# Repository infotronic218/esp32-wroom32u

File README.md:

"# esp32-wroom32u" 
"# esp32-wroom32u"

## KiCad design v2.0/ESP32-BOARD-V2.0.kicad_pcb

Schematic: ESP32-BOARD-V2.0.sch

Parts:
B1, B2: BUT; SW_Push_1P1T_NO_CK_KMR2; MPN KMR221GLFS; Mouser 611-KMR221G-LFS
C1, C2, C5, C9, C14: 1uF; C_0805_2012Metric; MPN EMK212B7105KG-T; Mouser 963-EMK212B7105KG-T
C3, C4, C7, C8, C11, C12, C13, C16: 100nF; C_0603_1608Metric; MPN C0603C104J4RAC; Mouser 80-C0603C104J4RAC
C6, C10, C15: 10uF; C_1206_3216Metric; MPN C1206C106K8PAC; Mouser 80-C1206C106K8PAC
D1, D4, D5, D6: RED; LED_0805_2012Metric; MPN AP2012HD; Mouser 604-AP2012HD
D2: YELLOW; LED_0805_2012Metric; MPN AP2012YD; Mouser 604-AP2012YD
D3, D9: GREEN; LED_0805_2012Metric; MPN 150080GS75000; Mouser 710-150080GS75000
D7: IN-PI554FCH; LED-DIGITAL-IN-PI554FCH; MPN IN-PI554FCH; Mouser 743-IN-PI554FCH
D8: RB060LAM-40TFTR; D_SOD-128; MPN RB060LAM-40TFTR; Mouser 755-RB060LAM-40TFTR
H1, H2, H3, H4: Mount; MountingHole_2.2mm_M2_Pad
J1: PIR SENSOR; PinSocket_1x03_P2.54mm_Vertical
J2: OLED-128X64; PinSocket_1x04_P2.54mm_Vertical
J3: PROG; PinHeader_1x04_P2.54mm_Vertical
J4: BATT; JST_XH_B2B-XH-A_1x02_P2.50mm_Vertical
J5: Conn_01x09; PinHeader_1x09_P2.54mm_Vertical
J6: UART; PinHeader_1x04_P2.54mm_Vertical
J7: SWITCH; SW_DIP_SPSTx04_Slide_Copal_CHS-04A_W5.08mm_P1.27mm_JPin; MPN CHS-04A; Mouser 229-CHS-04A
J8: CON_USB_GCT_USB4105_REVA; PARTREV 0.2; Mouser 640-USB4105-GF-A-060
JP1, JP2, JP3, JP4, JP5: WIRE; SolderJumper-2_P1.3mm_Open_RoundedPad1.0x1.5mm
L1: 2.2uH; L_1008_2520Metric_Pad1.43x2.20mm_HandSolder; MPN DFE252012P-2R2M=P2; Mouser 81-DFE252012P-2R2MP2
Q1: MBT3904DW1; SOT-363_SC-70-6
Q2: MIC94052YC6-TR; SOT-363_SC-70-6; MPN MIC94052YC6-TR; Mouser 998-MIC94052YC6TR
R1, R4, R5, R8, R10, R11, R27: 1.5K; R_0805_2012Metric; MPN RCC08051K50FKEA; Mouser 71-RCC08051K50FKEA
R2, R3: 470R; R_0805_2012Metric; MPN CR0805-FX-4700ELF; Mouser 652-CR0805FX-4700ELF
R6, R7, R9, R12, R13, R14, R15, R16, R17, R18, R19, R20, R21, R22, R24, R25, R26: 10K; R_0805_2012Metric; MPN CHP0805-FX-1002ELF; Mouser 652-CHP0805FX1002ELF
R23: 100K; R_0805_2012Metric; MPN CHP0805AFX-1003ELF; Mouser 652-CHP0805AFX1003EL
SW1: RST; SW_Push_1P1T_NO_CK_KMR2; MPN KMR221GLFS; Mouser 611-KMR221G-LFS
SW2: EN; SW_Push_1P1T_NO_CK_KMR2; MPN KMR221GLFS; Mouser 611-KMR221G-LFS
SW3: ON/OFF; SW_SPDT_PCM12; MPN PCM12SMTR; Mouser 611-PCM12SMTR
TH1: 10K; R_0805_2012Metric; MPN CRT0805-BY-1002ELF; Mouser 652-CRT0805BY1002ELF
U1: IC-BATT-CHARGER-MCP73834; DFN-10-1EP_3x3mm_P0.5mm_EP1.55x2.48mm; MPN MCP73834T-FCI/MF; Mouser 579-MCP73834T-FCI/MF
U2: ESP32-WROOM-32U; MPN ESP32-WROOM-32U(M113DH3200UH3Q0); Mouser 356-ESP32-WROOM-32U
U3: ADXL343; LGA-14_3x5mm_P0.8mm_LayoutBorder1x6y; MPN ADXL343BCCZ-RL7; Mouser 584-ADXL343BCCZ-R
U4: ISL9110IRTNZ; IC_BUCK_BOOST_ISL9110IRTNZ; MPN ISL9110IRTNZ; Mouser 968-ISL9110IRTNZ
U5: MIC280-3YM6-TR; SOT-23-6; MPN MIC280-3YM6-TR; Mouser 998-MIC280-3YM6TR
U6: CH340C; SOIC-16_3.9x9.9mm_P1.27mm

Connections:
+3V3: C3.1, C6.2, C7.1, C8.1, C9.2, C11.1, C15.2, C16.1, D7.3 (VDD), D9.2 (A), J1.1, J2.2 (VCC), J3.1, J5.1, J6.1, J7.5, J7.6, J7.7, J7.8, R18.1, R19.1, R24.1, R25.1, R26.1, TH1.1, U2.2 (3V3), U3.1 (Vdd_I/O), U3.6 (Vs), U3.7 (~CS), U4.1 (VOUT), U4.12 (FB), U5.1 (VDD)
+BATT: C2.1, C4.1, J4.1, Q2.1 (D), Q2.2 (S), Q2.5 (D), Q2.6 (D), U1.9 (VBAT), U1.10 (VBAT)
/D+: J8.A6 (DP1), J8.B6 (DP2), U6.5 (UD+)
/D-: J8.A7 (DN1), J8.B7 (DN2), U6.6 (UD-)
B1: B1.2, R14.1, U2.6 (I034)
B2: B2.2, R12.1, U2.7 (I035)
EN: C5.2, Q1.6 (C1), R19.2, SW2.2, U2.3 (EN)
GND: B1.1, B2.1, C1.2, C2.2, C3.2, C4.2, C5.1, C6.1, C7.2, C8.2, C9.1, C10.1, C11.2, C12.1, C13.2, C14.1, C15.1, C16.2, D7.1 (VSS), J1.3, J2.1 (GND), J3.4, J4.2, J5.9, J6.4, J8.A1/B12 (GND), J8.B1/A12 (GND), J8.G1 (GND), J8.G2 (GND), J8.G3 (GND), J8.G4 (GND), JP2.2, JP4.2, JP5.2, R1.2, R4.2, R5.2, R8.2, R9.2, R12.2, R13.2, R14.2, R15.2, R16.2, R17.2, R20.2, R23.2, R27.2, SW1.1, SW2.1, SW3.1 (A), U1.5 (VSS), U1.11 (PAD), U2.1 (GND), U2.15 (GND), U2.38 (GND), U2.G.1 (GND), U2.G.2 (GND), U2.G.4 (GND), U2.G.5 (GND), U2.G.6 (GND), U2.G.7 (GND), U2.G.8 (GND), U2.G.9 (GND), U2.G.10 (GND), U2.G.11 (GND), U2.G.12 (GND), U2.G.13 (GND), U2.G.14 (GND), U2.G.15 (GND), U2.G.16 (GND), U2.G.17 (GND), U2.G.18 (GND), U2.G.19 (GND), U2.G.20 (GND), U2.G.21 (GND), U2.G.22 (GND), U3.2 (GND), U3.4 (GND), U3.5 (GND), U3.12 (SDO/ADDR), U4.3 (PGND), U4.11 (GND), U4.13 (PAD), U5.2 (GND), U6.1 (GND)
INT: R24.2, U5.6 (~INT)
IO0: Q1.3 (C2), R18.2, SW1.2, U2.25 (IO0)
IO2: J5.7, U2.24 (IO2)
IO4: J5.8, U2.26 (IO4)
IO12: J5.5, U2.14 (IO12)
IO13_ADC2_CH4_NTC: R20.1, TH1.2, U2.16 (IO13)
IO14: J5.6, U2.13 (IO14)
IO15_PIR_IN: J1.2, U2.23 (IO15)
IO16_U2RXD: J6.2, U2.27 (IO16)
IO17_U2TXD: J6.3, U2.28 (IO17)
IO21_I2C_SDA: J2.4 (SDA), R25.2, U2.33 (IO21), U3.13 (SDA/SDI/SDIO), U5.5 (DATA)
IO22_I2C_SCL: J2.3 (SCL), R26.2, U2.36 (IO22), U3.14 (SCL/SCLK), U5.4 (CLK)
LED1: D1.2 (A), U2.31 (IO19)
LED2: D4.2 (A), U2.30 (IO18)
LED3: D5.2 (A), U2.29 (IO5)
LED4: J5.4, JP3.1, U2.37 (IO23)
LED_IN: D7.2 (DIN), U2.8 (I032)
unnamed: C10.2, D8.1 (K), Q2.4 (S), SW3.3 (C), U4.5 (PVIN), U4.6 (VIN), U4.10 (MODE/SYNC)
unnamed: C12.2, U6.4 (V3)
unnamed: D1.1 (K), R1.1
unnamed: D2.1 (K), R2.2
unnamed: D3.1 (K), R3.2
unnamed: D4.1 (K), R4.1
unnamed: D5.1 (K), R5.1
unnamed: D6.1 (K), R8.1
unnamed: D6.2 (A), JP3.2
unnamed: D9.1 (K), R27.1
unnamed: JP1.2, R6.1
unnamed: JP2.1, R7.2
unnamed: JP4.1, R10.2
unnamed: JP5.1, R11.2
unnamed: L1.1, U4.4 (LX1)
unnamed: L1.2, U4.2 (LX2)
unnamed: Q1.2 (B1), R21.1
unnamed: Q1.5 (B2), R22.1
unnamed: R2.1, U1.3 (STAT1)
unnamed: R3.1, U1.4 (STAT2)
unnamed: R6.2, R7.1, U1.7 (~PG)
unnamed: R9.1, U1.8 (THERM)
unnamed: R10.1, R11.1, U1.6 (PROG)
unnamed: SW3.2 (B), U4.9 (EN)
S1: J7.1, R13.1, U2.9 (I033)
S2: J7.2, R15.1, U2.10 (I025)
S3: J7.3, R16.1, U2.11 (I026)
S4: J7.4, R17.1, U2.12 (IO27)
U0RXD: J3.2, U2.35 (TXD0), U6.2 (TXD)
U0TXD: J3.3, U2.34 (RXD0), U6.3 (RXD)
VBUS: C1.1, C13.1, C14.2, D2.2 (A), D3.2 (A), D8.2 (A), J8.A4/B9 (VBUS), J8.B4/A9 (VBUS), JP1.1, Q2.3 (G), R23.1, U1.1 (VDD), U1.2 (VDD), U6.16 (VCC)
VN: J5.3, U2.5 (SENSOR_VN)
VP: J5.2, U2.4 (SENSOR_VP)
~DTR: Q1.4 (E2), R21.2, U6.13 (~DTR)
~RTS: Q1.1 (E1), R22.2, U6.14 (~RTS)

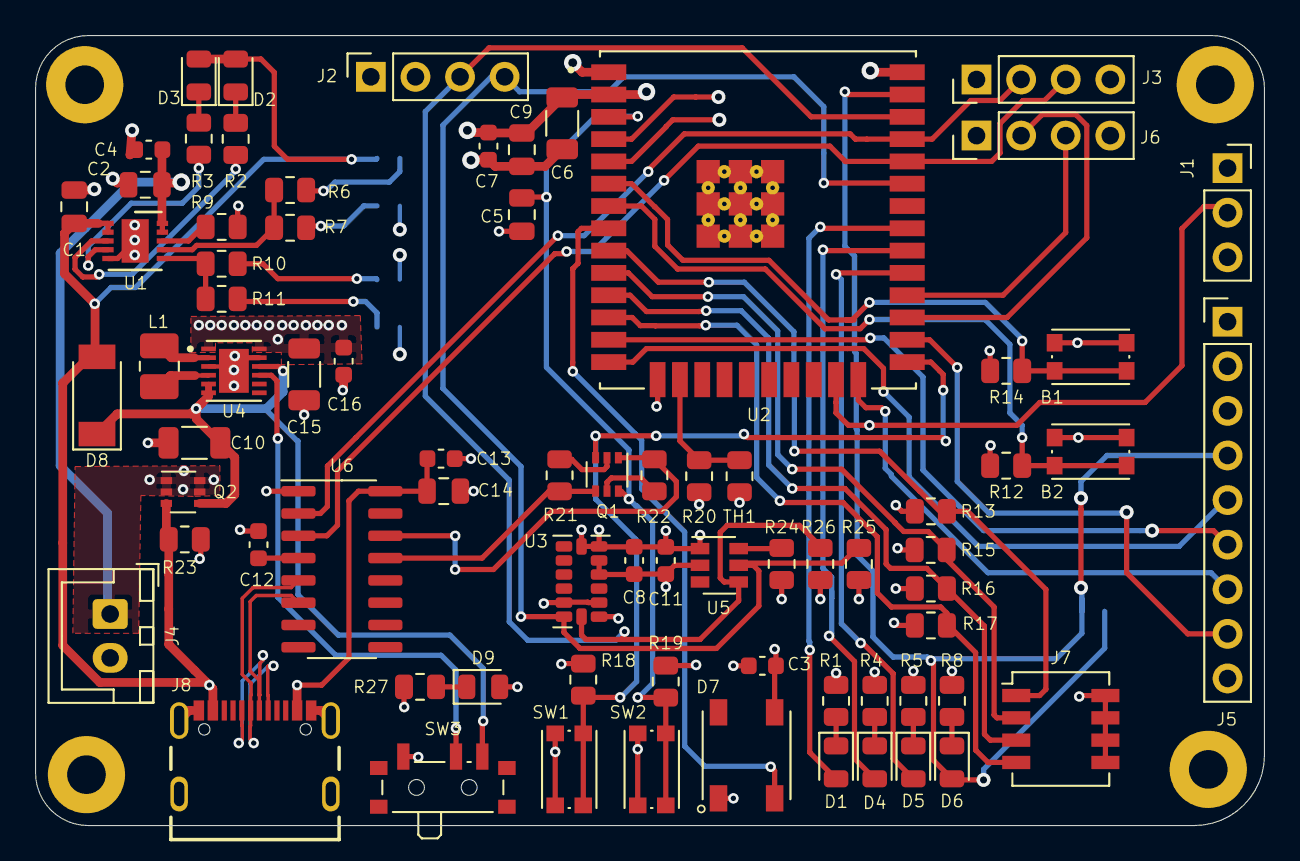
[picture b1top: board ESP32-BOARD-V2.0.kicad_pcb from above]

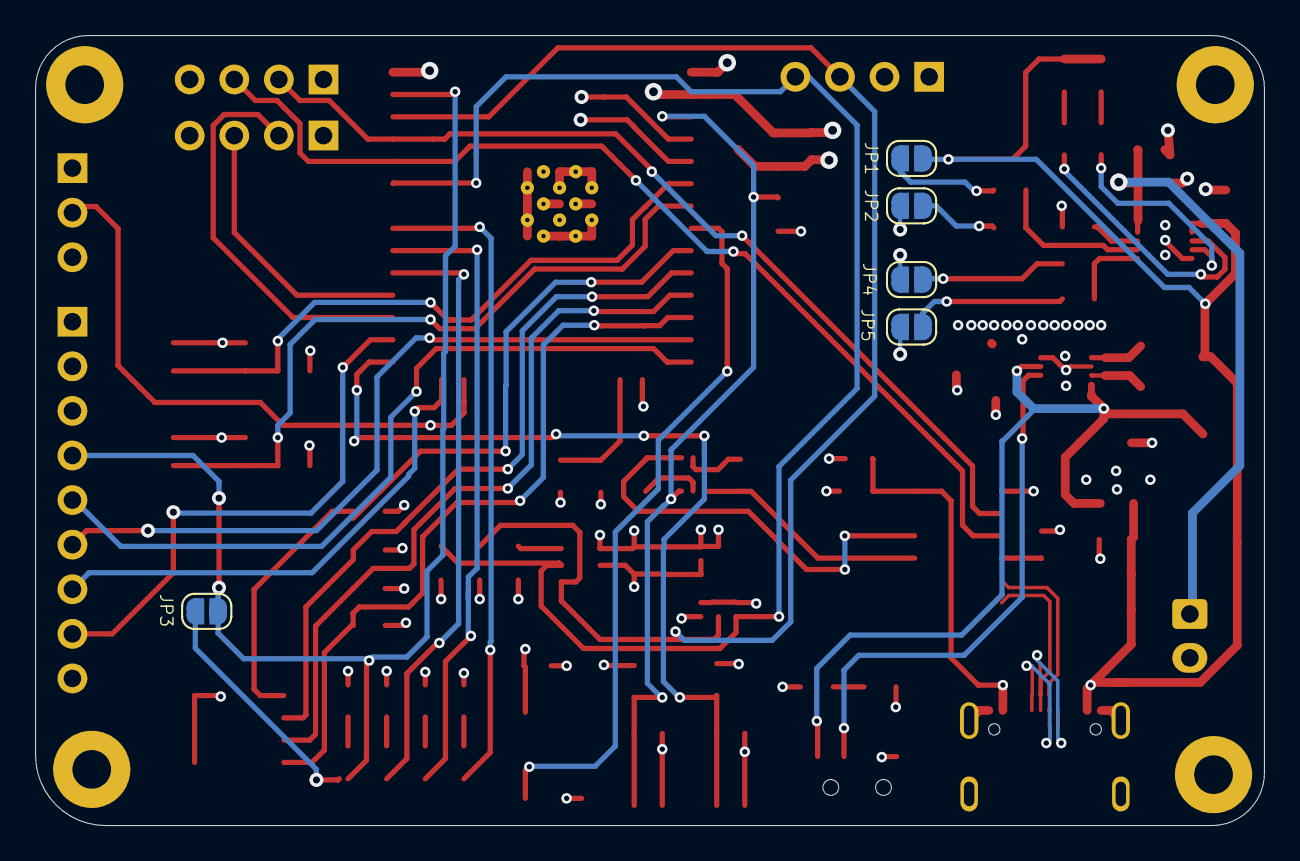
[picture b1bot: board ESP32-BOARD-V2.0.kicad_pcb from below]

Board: 4 copper layers, 70.0 x 45.0 mm, 84 parts (5 on the bottom side), 60 nets.

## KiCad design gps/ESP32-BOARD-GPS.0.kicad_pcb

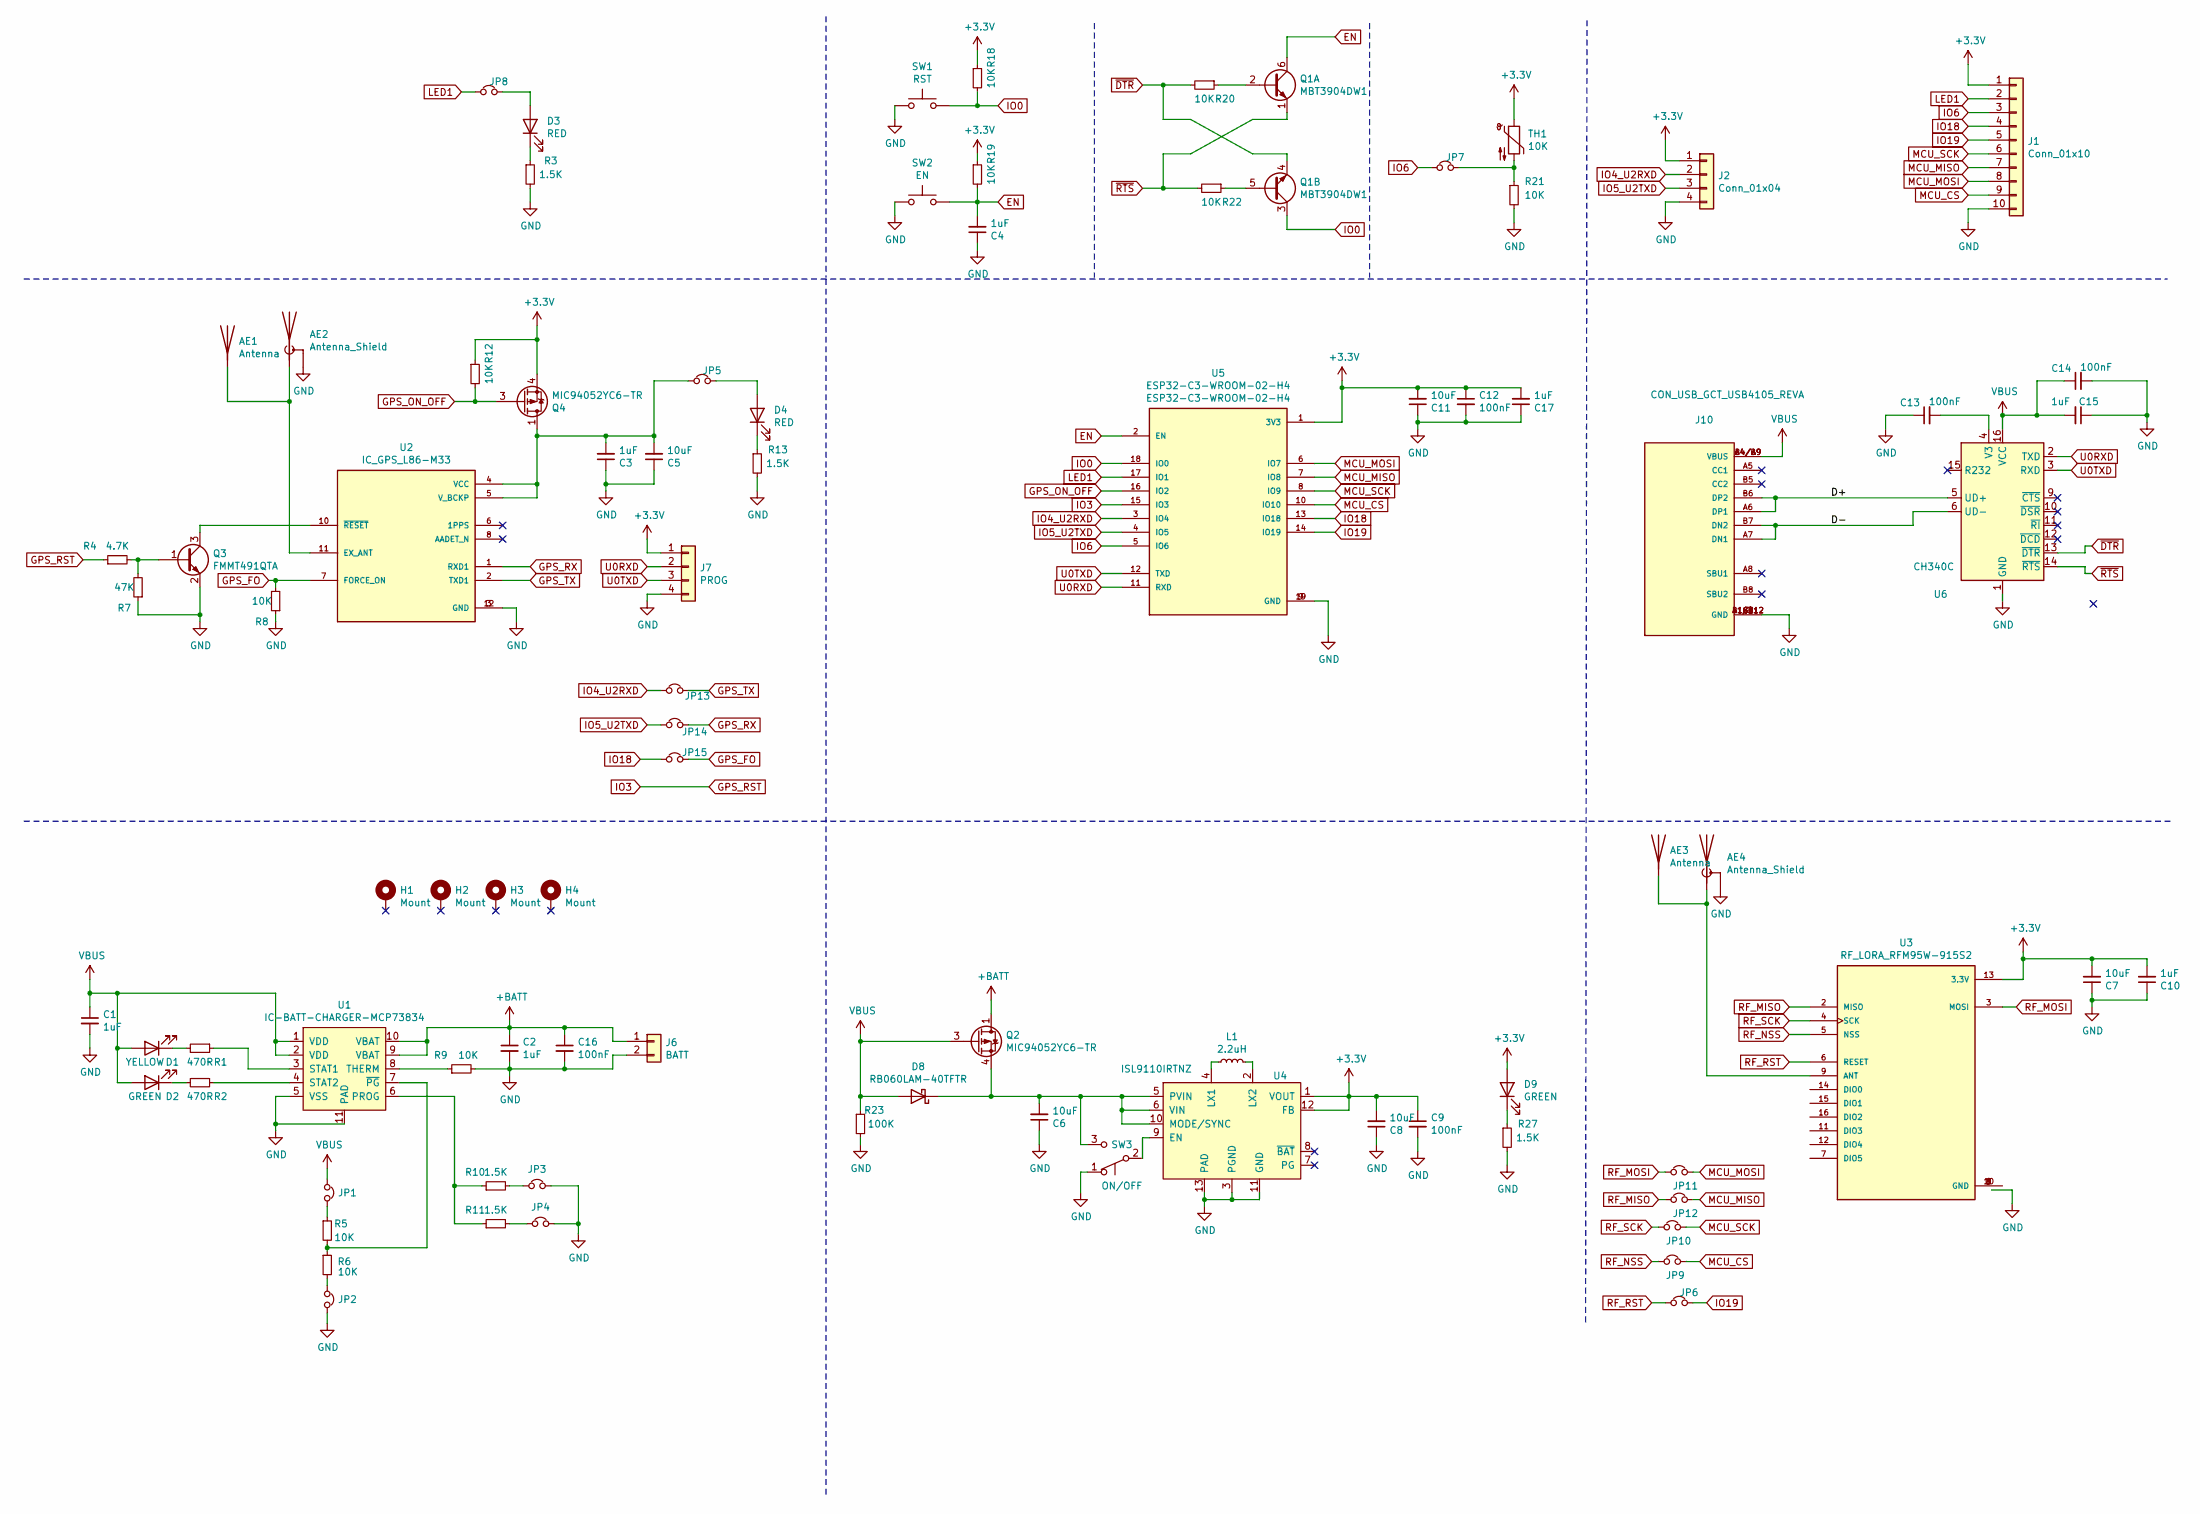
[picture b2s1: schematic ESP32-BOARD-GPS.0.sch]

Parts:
AE1, AE3: Antenna; PinHeader_1x01_P2.54mm_Vertical
AE2, AE4: Antenna_Shield; U.FL_Hirose_U.FL-R-SMT-1_Vertical
C1, C2, C3, C4, C10, C15, C17: 1uF; C_0805_2012Metric; MPN EMK212B7105KG-T; Mouser 963-EMK212B7105KG-T
C5, C6, C7, C8, C11: 10uF; C_1206_3216Metric; MPN C1206C106K8PAC; Mouser 80-C1206C106K8PAC
C9, C12, C13, C14, C16: 100nF; C_0603_1608Metric; MPN C0603C104J4RAC; Mouser 80-C0603C104J4RAC
D1: YELLOW; LED_0805_2012Metric; MPN AP2012YD; Mouser 604-AP2012YD
D2, D9: GREEN; LED_0805_2012Metric; MPN 150080GS75000; Mouser 710-150080GS75000
D3, D4: RED; LED_0805_2012Metric; MPN AP2012HD; Mouser 604-AP2012HD
D8: RB060LAM-40TFTR; D_SOD-128; MPN RB060LAM-40TFTR; Mouser 755-RB060LAM-40TFTR
H1, H2, H3, H4: Mount; MountingHole_2.2mm_M2_Pad
J1: Conn_01x10; PinHeader_1x10_P2.54mm_Vertical
J2: Conn_01x04; PinHeader_1x04_P2.54mm_Vertical
J6: BATT; JST_XH_B2B-XH-A_1x02_P2.50mm_Vertical
J7: PROG; PinHeader_1x04_P2.54mm_Vertical
J10: CON_USB_GCT_USB4105_REVA; PARTREV 0.2; Mouser 640-USB4105-GF-A-060
JP1, JP2, JP3, JP4, JP5, JP6, JP7, JP8, JP9, JP10, JP11, JP12, JP13, JP14, JP15: WIRE; SolderJumper-2_P1.3mm_Open_RoundedPad1.0x1.5mm
L1: 2.2uH; L_1008_2520Metric_Pad1.43x2.20mm_HandSolder; MPN DFE252012P-2R2M=P2; Mouser 81-DFE252012P-2R2MP2
Q1: MBT3904DW1; SOT-363_SC-70-6
Q2, Q4: MIC94052YC6-TR; SOT-363_SC-70-6; MPN MIC94052YC6-TR; Mouser 998-MIC94052YC6TR
Q3: FMMT491QTA; SOT-23
R1, R2: 470R; R_0805_2012Metric; MPN CR0805-FX-4700ELF; Mouser 652-CR0805FX-4700ELF
R3, R10, R11, R13, R27: 1.5K; R_0805_2012Metric; MPN RCC08051K50FKEA; Mouser 71-RCC08051K50FKEA
R4: 4.7K; R_0805_2012Metric; MPN CRGCQ0805F4K7; Mouser 279-CRGCQ0805F4K7
R5, R6, R8, R9, R12, R18, R19, R20, R21, R22: 10K; R_0805_2012Metric; MPN CR0805-FX-1002ELF; Mouser 652-CR0805FX-1002ELF
R7: 47K; R_0805_2012Metric; MPN CRGCQ0805F47K; Mouser 279-CRGCQ0805F47K
R23: 100K; R_0805_2012Metric; MPN CHP0805AFX-1003ELF; Mouser 652-CHP0805AFX1003EL
SW1: RST; SW_Push_1P1T_NO_CK_KMR2; MPN KMR221GLFS; Mouser 611-KMR221G-LFS
SW2: EN; SW_Push_1P1T_NO_CK_KMR2; MPN KMR221GLFS; Mouser 611-KMR221G-LFS
SW3: ON/OFF; SW_SPDT_PCM12; MPN PCM12SMTR; Mouser 611-PCM12SMTR
TH1: 10K; R_0805_2012Metric; MPN CRT0805-BY-1002ELF; Mouser 652-CRT0805BY1002ELF
U1: IC-BATT-CHARGER-MCP73834; DFN-10-1EP_3x3mm_P0.5mm_EP1.55x2.48mm; MPN MCP73834T-FCI/MF; Mouser 579-MCP73834T-FCI/MF
U2: IC_GPS_L86-M33
U3: RF_LORA_RFM95W-915S2
U4: ISL9110IRTNZ; IC_BUCK_BOOST_ISL9110IRTNZ; MPN ISL9110IRTNZ; Mouser 968-ISL9110IRTNZ
U5: ESP32-C3-WROOM-02-H4; MPN ESP32-C3-WROOM-02-H4
U6: CH340C; SOIC-16_3.9x9.9mm_P1.27mm

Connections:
+3V3: C7.2, C8.2, C9.1, C10.2, C11.2, C12.1, C17.2, D9.2 (A), J1.1, J2.1, J7.1, Q4.4 (S), R12.1, R18.1, R19.1, TH1.1, U3.13 (3.3V), U4.1 (VOUT), U4.12 (FB), U5.1 (3V3)
+BATT: C2.1, C16.1, J6.1, Q2.1 (D), Q2.2 (S), Q2.5 (D), Q2.6 (D), U1.9 (VBAT), U1.10 (VBAT)
/D+: J10.A6 (DP1), J10.B6 (DP2), U6.5 (UD+)
/D-: J10.A7 (DN1), J10.B7 (DN2), U6.6 (UD-)
EN: C4.2, Q1.6 (C1), R19.2, SW2.2, U5.2 (EN)
GPS_ON_OFF: Q4.3 (G), R12.2, U5.16 (IO2)
GPS_RST: R4.1, U5.15 (IO3)
GPS_RX: JP14.2, U2.1 (RXD1)
GPS_TX: JP13.2, U2.2 (TXD1)
IO0: Q1.3 (C2), R18.2, SW1.2, U5.18 (IO0)
IO4_U2RXD: J2.2, JP13.1, U5.3 (IO4)
IO5_U2TXD: J2.3, JP14.1, U5.4 (IO5)
IO6: J1.3, JP7.1, U5.5 (IO6)
IO19: J1.5, JP6.2, U5.14 (IO19)
LED1: J1.2, JP8.1, U5.17 (IO1)
MCU_CS: J1.9, JP9.2, U5.10 (IO10)
MCU_MISO: J1.7, JP12.2, U5.7 (IO8)
MCU_MOSI: J1.8, JP11.2, U5.6 (IO7)
MCU_SCK: J1.6, JP10.2, U5.8 (IO9)
unnamed: AE1.1, AE2.1 (A), U2.11 (EX_ANT)
unnamed: AE3.1, AE4.1 (A), U3.9 (ANT)
unnamed: C3.2, C5.2, JP5.1, Q4.1 (D), Q4.2 (S), Q4.5 (D), Q4.6 (D), U2.4 (VCC), U2.5 (V_BCKP)
unnamed: C6.2, D8.1 (K), Q2.4 (S), SW3.3 (C), U4.5 (PVIN), U4.6 (VIN), U4.10 (MODE/SYNC)
unnamed: C13.2, U6.4 (V3)
unnamed: D1.1 (K), R1.2
unnamed: D2.1 (K), R2.2
unnamed: D3.1 (K), R3.1
unnamed: D3.2 (A), JP8.2
unnamed: D4.1 (K), R13.1
unnamed: D4.2 (A), JP5.2
unnamed: D9.1 (K), R27.1
unnamed: JP1.2, R5.1
unnamed: JP2.1, R6.2
unnamed: JP3.1, R10.2
unnamed: JP4.1, R11.2
unnamed: JP7.2, R21.1, TH1.2
unnamed: L1.1, U4.4 (LX1)
unnamed: L1.2, U4.2 (LX2)
unnamed: Q1.2 (B1), R20.1
unnamed: Q1.5 (B2), R22.1
unnamed: Q3.1 (B), R4.2, R7.2
unnamed: Q3.3 (C), U2.10 (~RESET)
unnamed: R1.1, U1.3 (STAT1)
unnamed: R2.1, U1.4 (STAT2)
unnamed: R5.2, R6.1, U1.7 (~PG)
unnamed: R9.1, U1.8 (THERM)
unnamed: R10.1, R11.1, U1.6 (PROG)
unnamed: SW3.2 (B), U4.9 (EN)
RF_MISO: JP12.1, U3.2 (MISO)
RF_MOSI: JP11.1, U3.3 (MOSI)
RF_NSS: JP9.1, U3.5 (NSS)
RF_RST: JP6.1, U3.6 (RESET)
RF_SCK: JP10.1, U3.4 (SCK)
U0RXD: J7.2, U5.11 (RXD), U6.2 (TXD)
U0TXD: J7.3, U5.12 (TXD), U6.3 (RXD)
VBUS: C1.1, C14.1, C15.2, D1.2 (A), D2.2 (A), D8.2 (A), J10.A4/B9 (VBUS), J10.B4/A9 (VBUS), JP1.1, Q2.3 (G), R23.1, U1.1 (VDD), U1.2 (VDD), U6.16 (VCC)
~DTR: Q1.4 (E2), R20.2, U6.13 (~DTR)
~RTS: Q1.1 (E1), R22.2, U6.14 (~RTS)

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
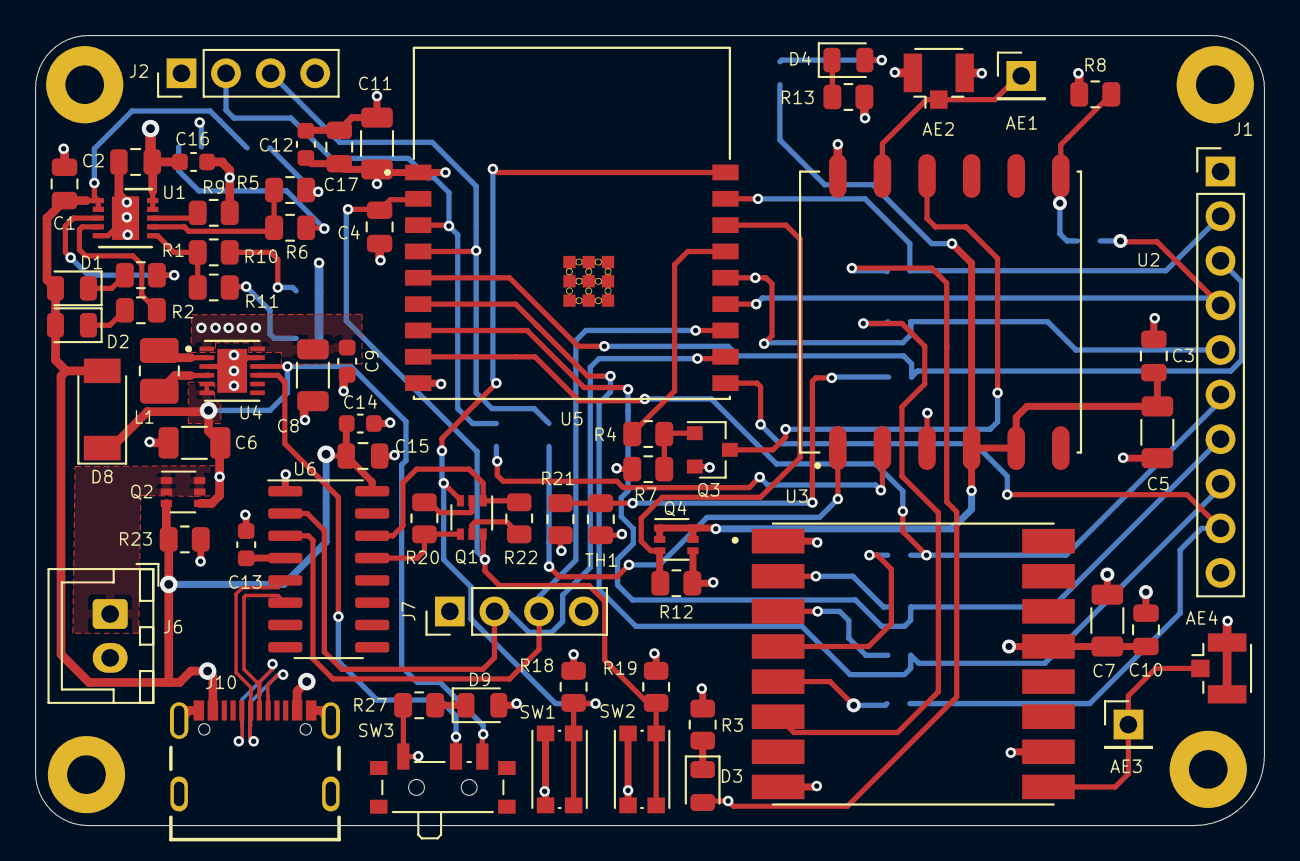
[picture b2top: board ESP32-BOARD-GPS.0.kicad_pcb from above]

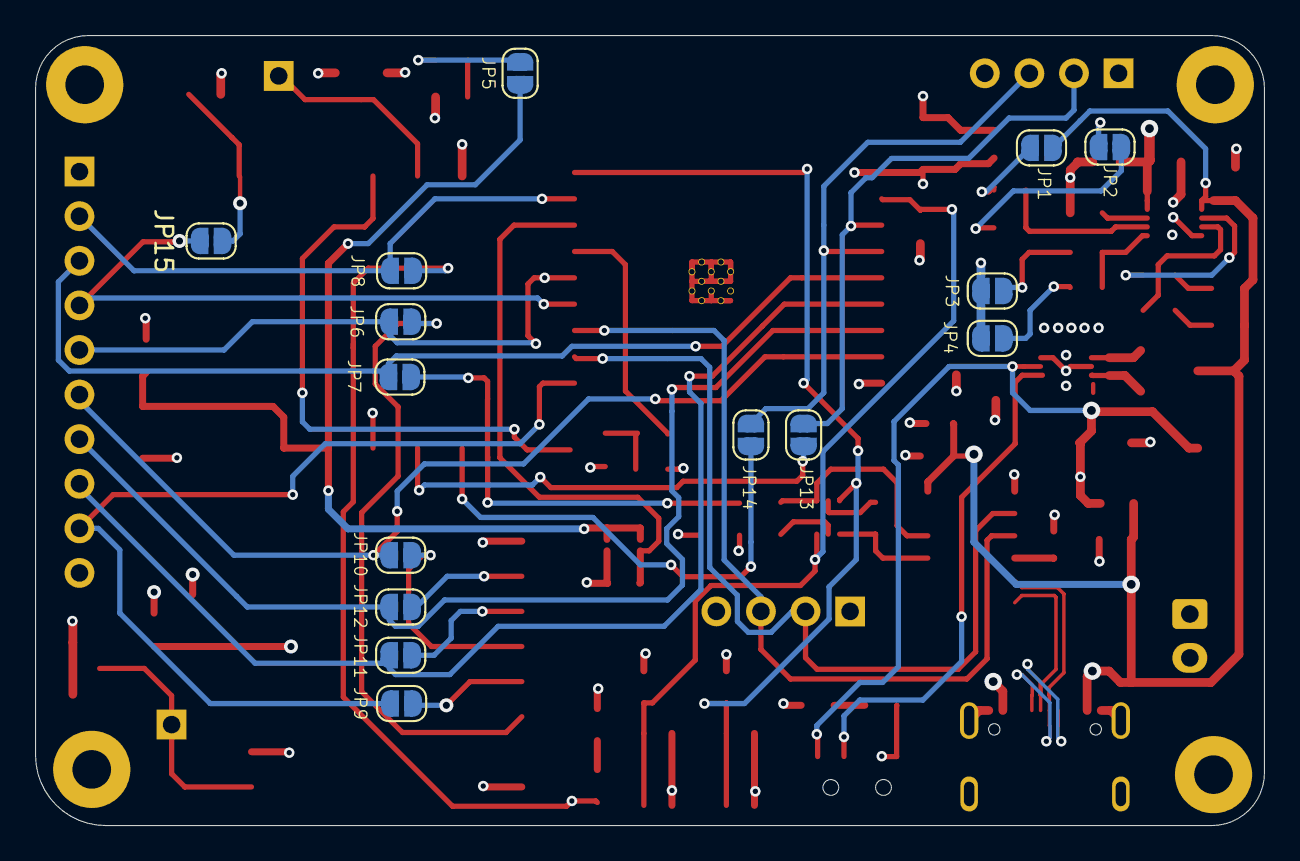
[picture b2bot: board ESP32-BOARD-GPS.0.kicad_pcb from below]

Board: 4 copper layers, 70.0 x 45.0 mm, 86 parts (15 on the bottom side), 61 nets.

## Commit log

2021-12-20 Update the design
